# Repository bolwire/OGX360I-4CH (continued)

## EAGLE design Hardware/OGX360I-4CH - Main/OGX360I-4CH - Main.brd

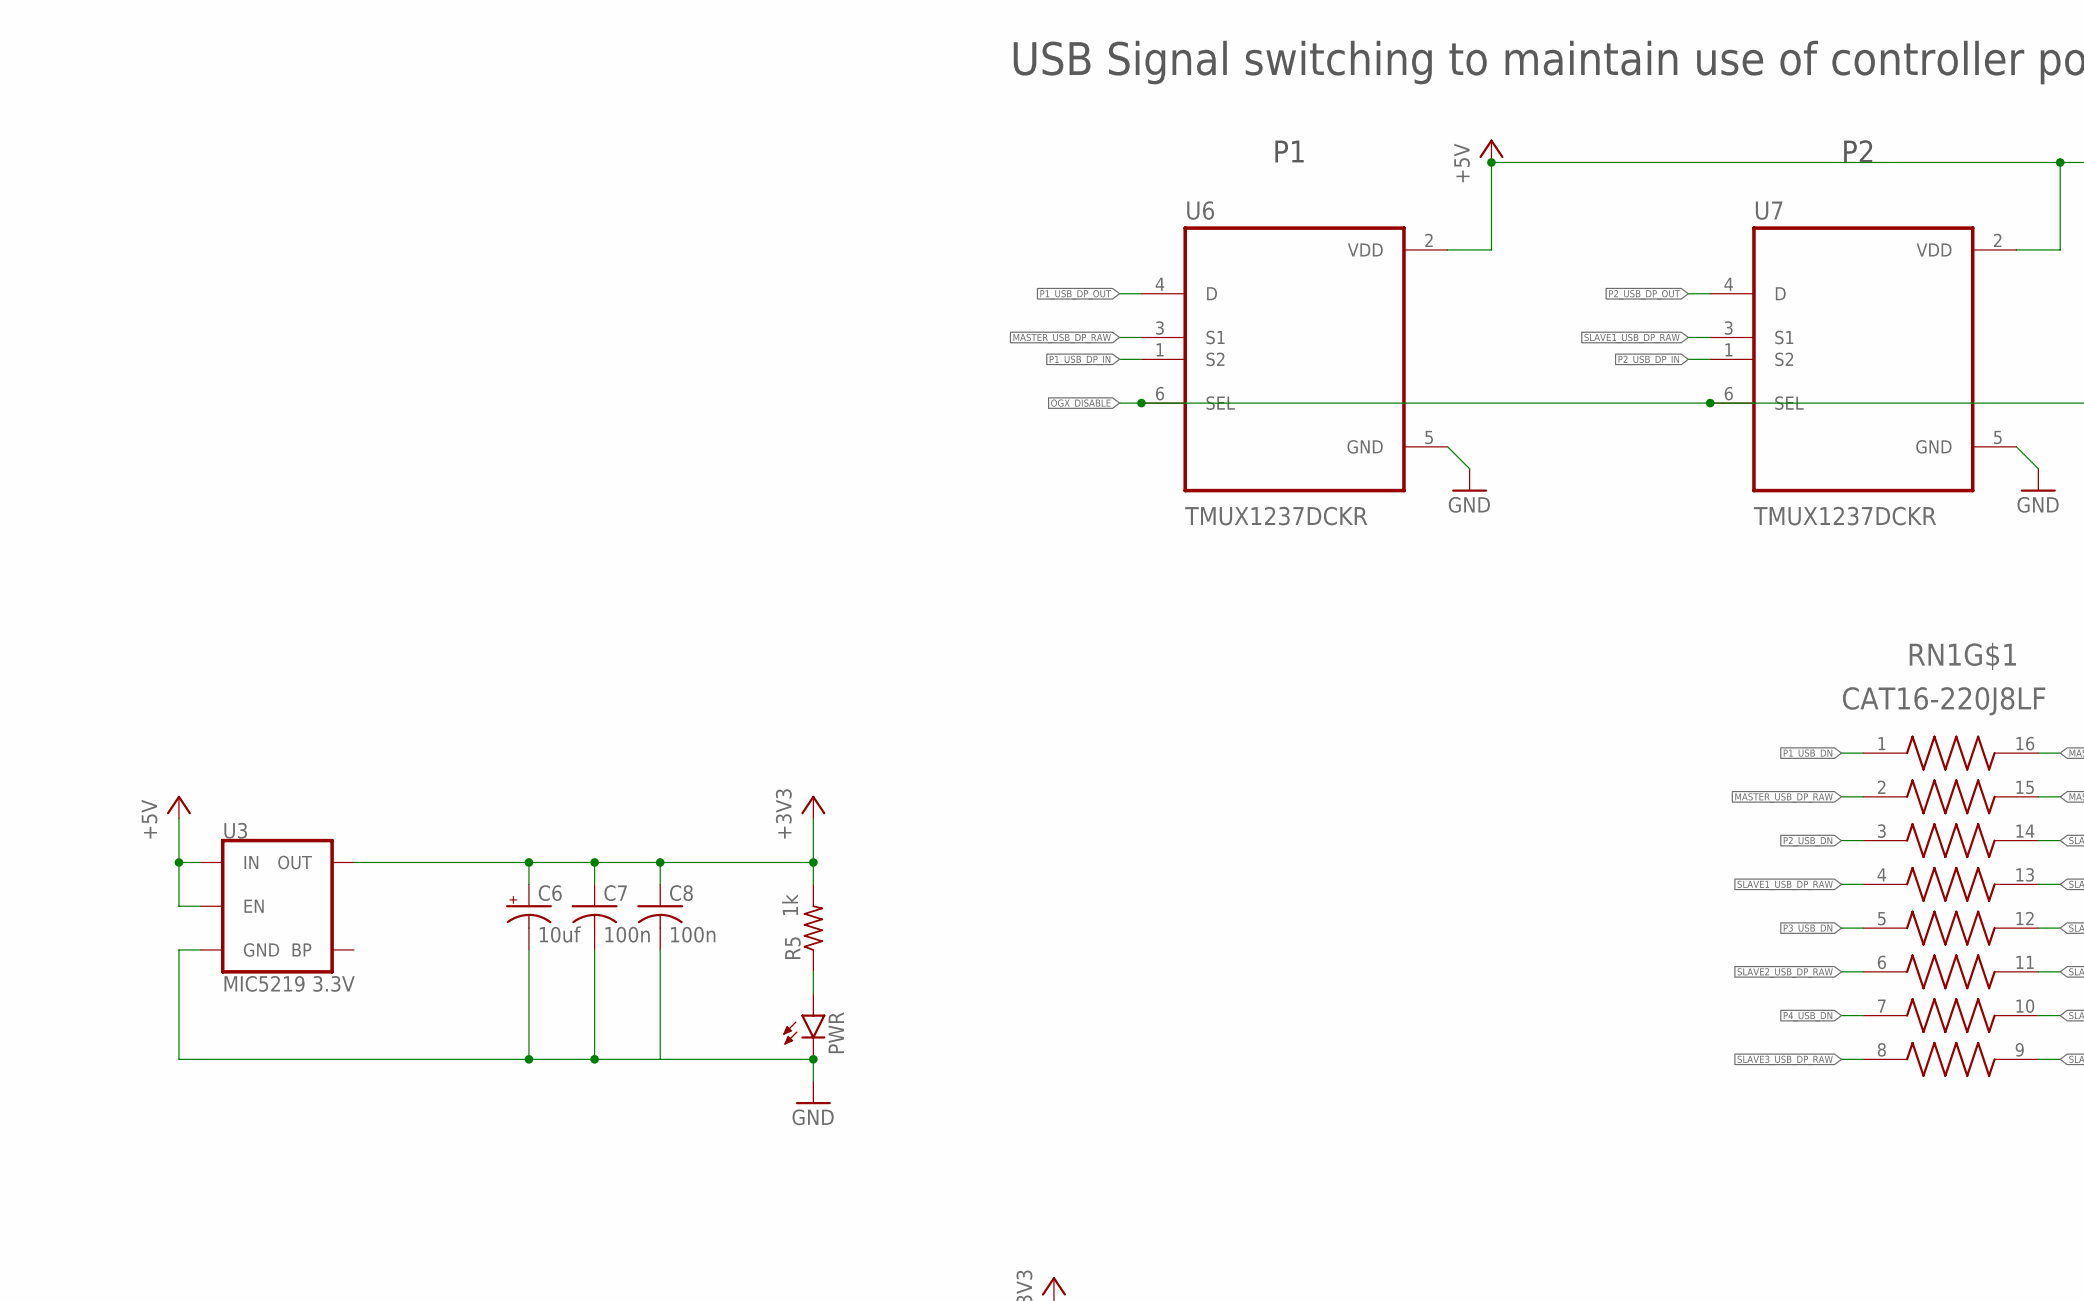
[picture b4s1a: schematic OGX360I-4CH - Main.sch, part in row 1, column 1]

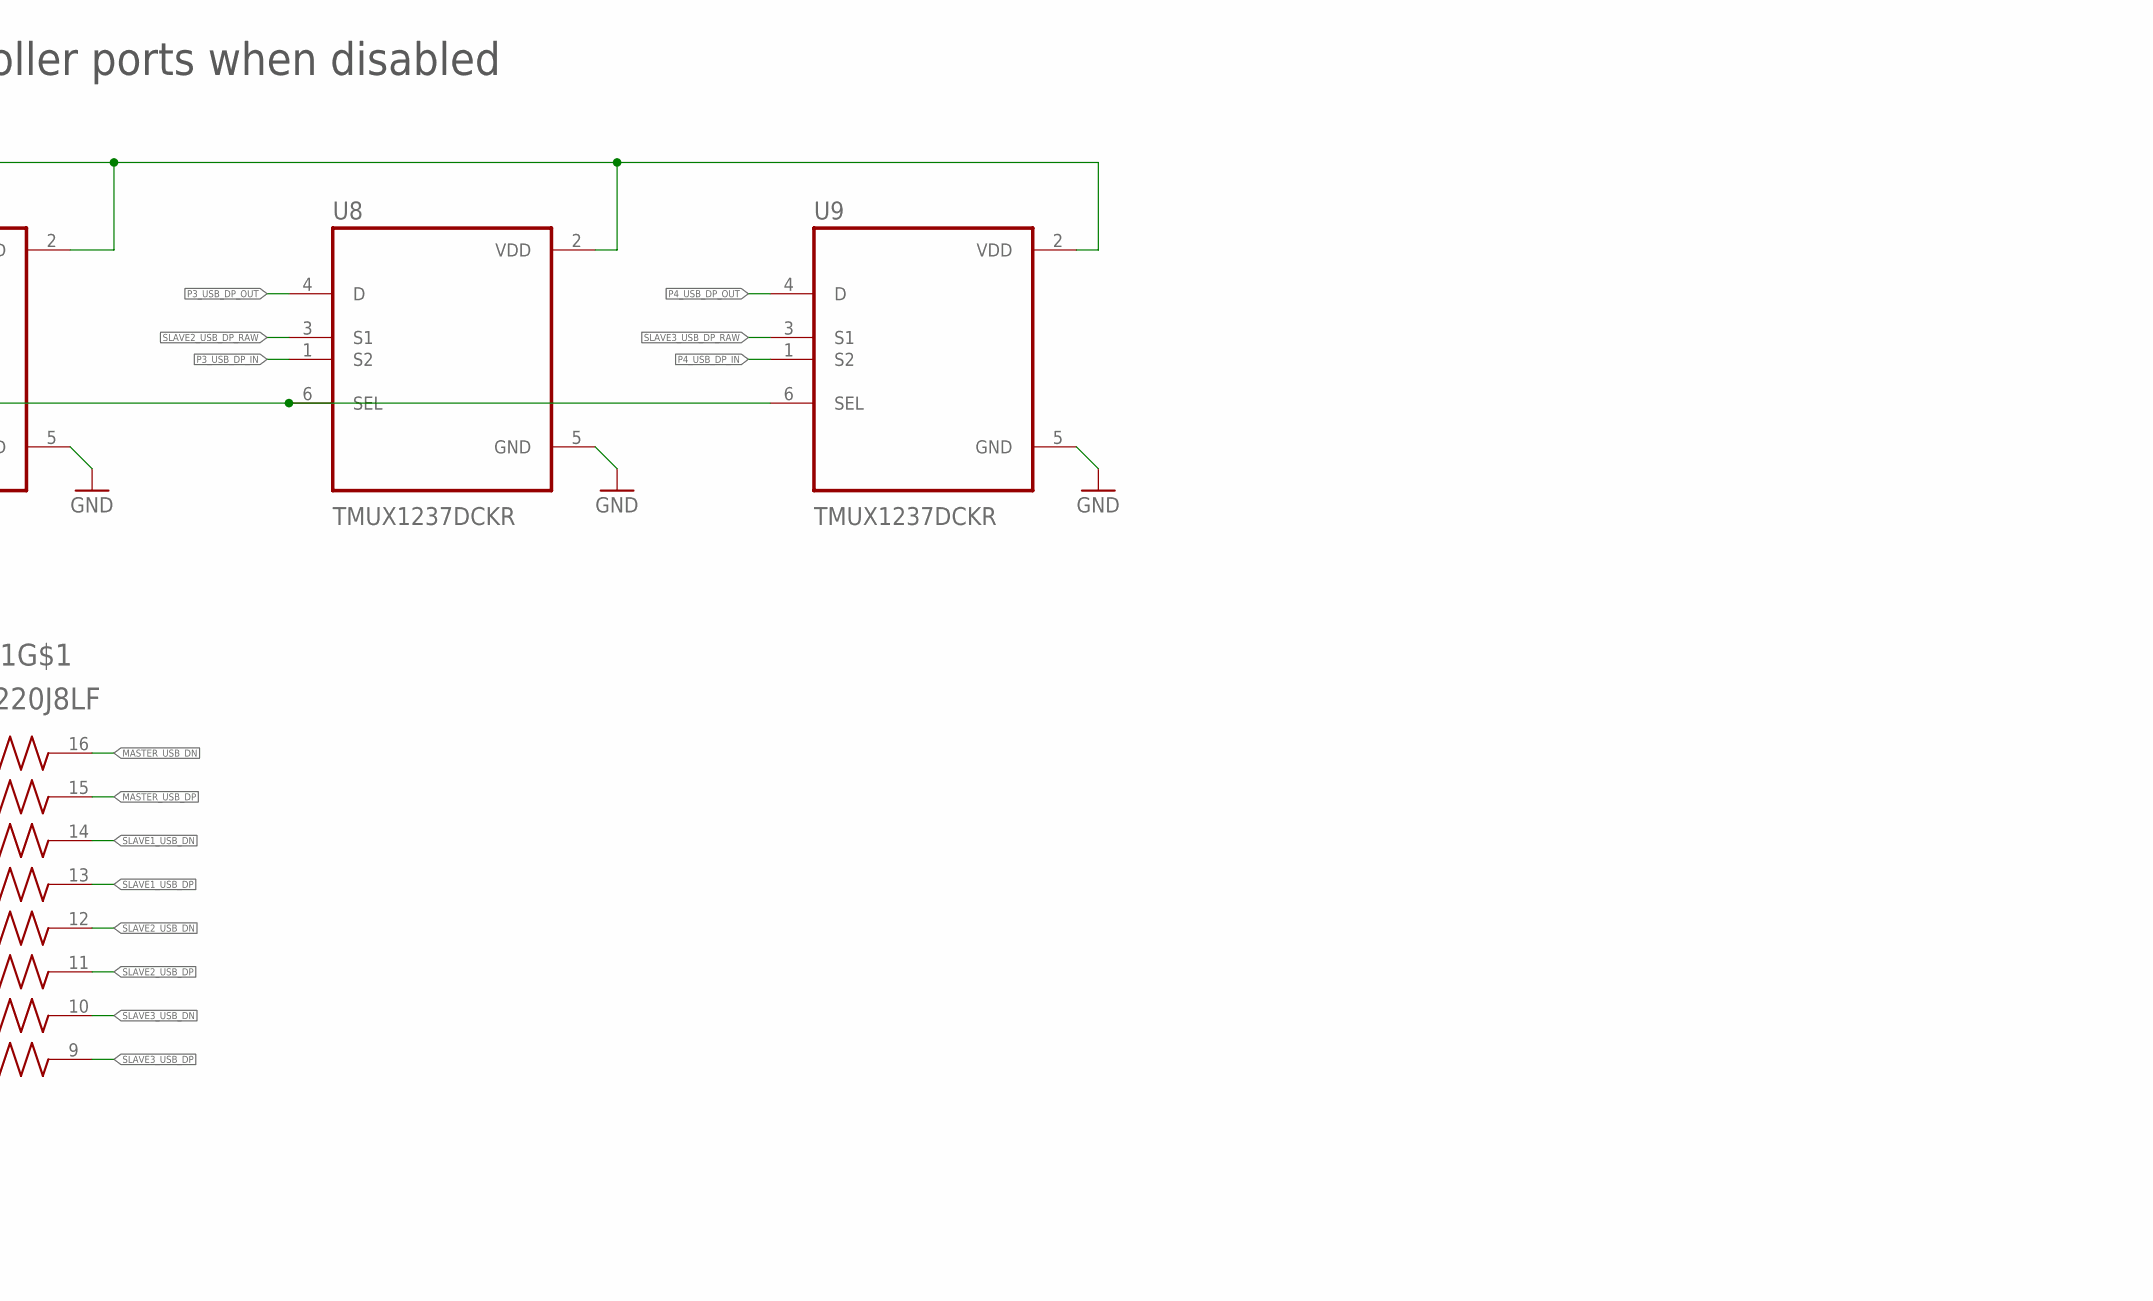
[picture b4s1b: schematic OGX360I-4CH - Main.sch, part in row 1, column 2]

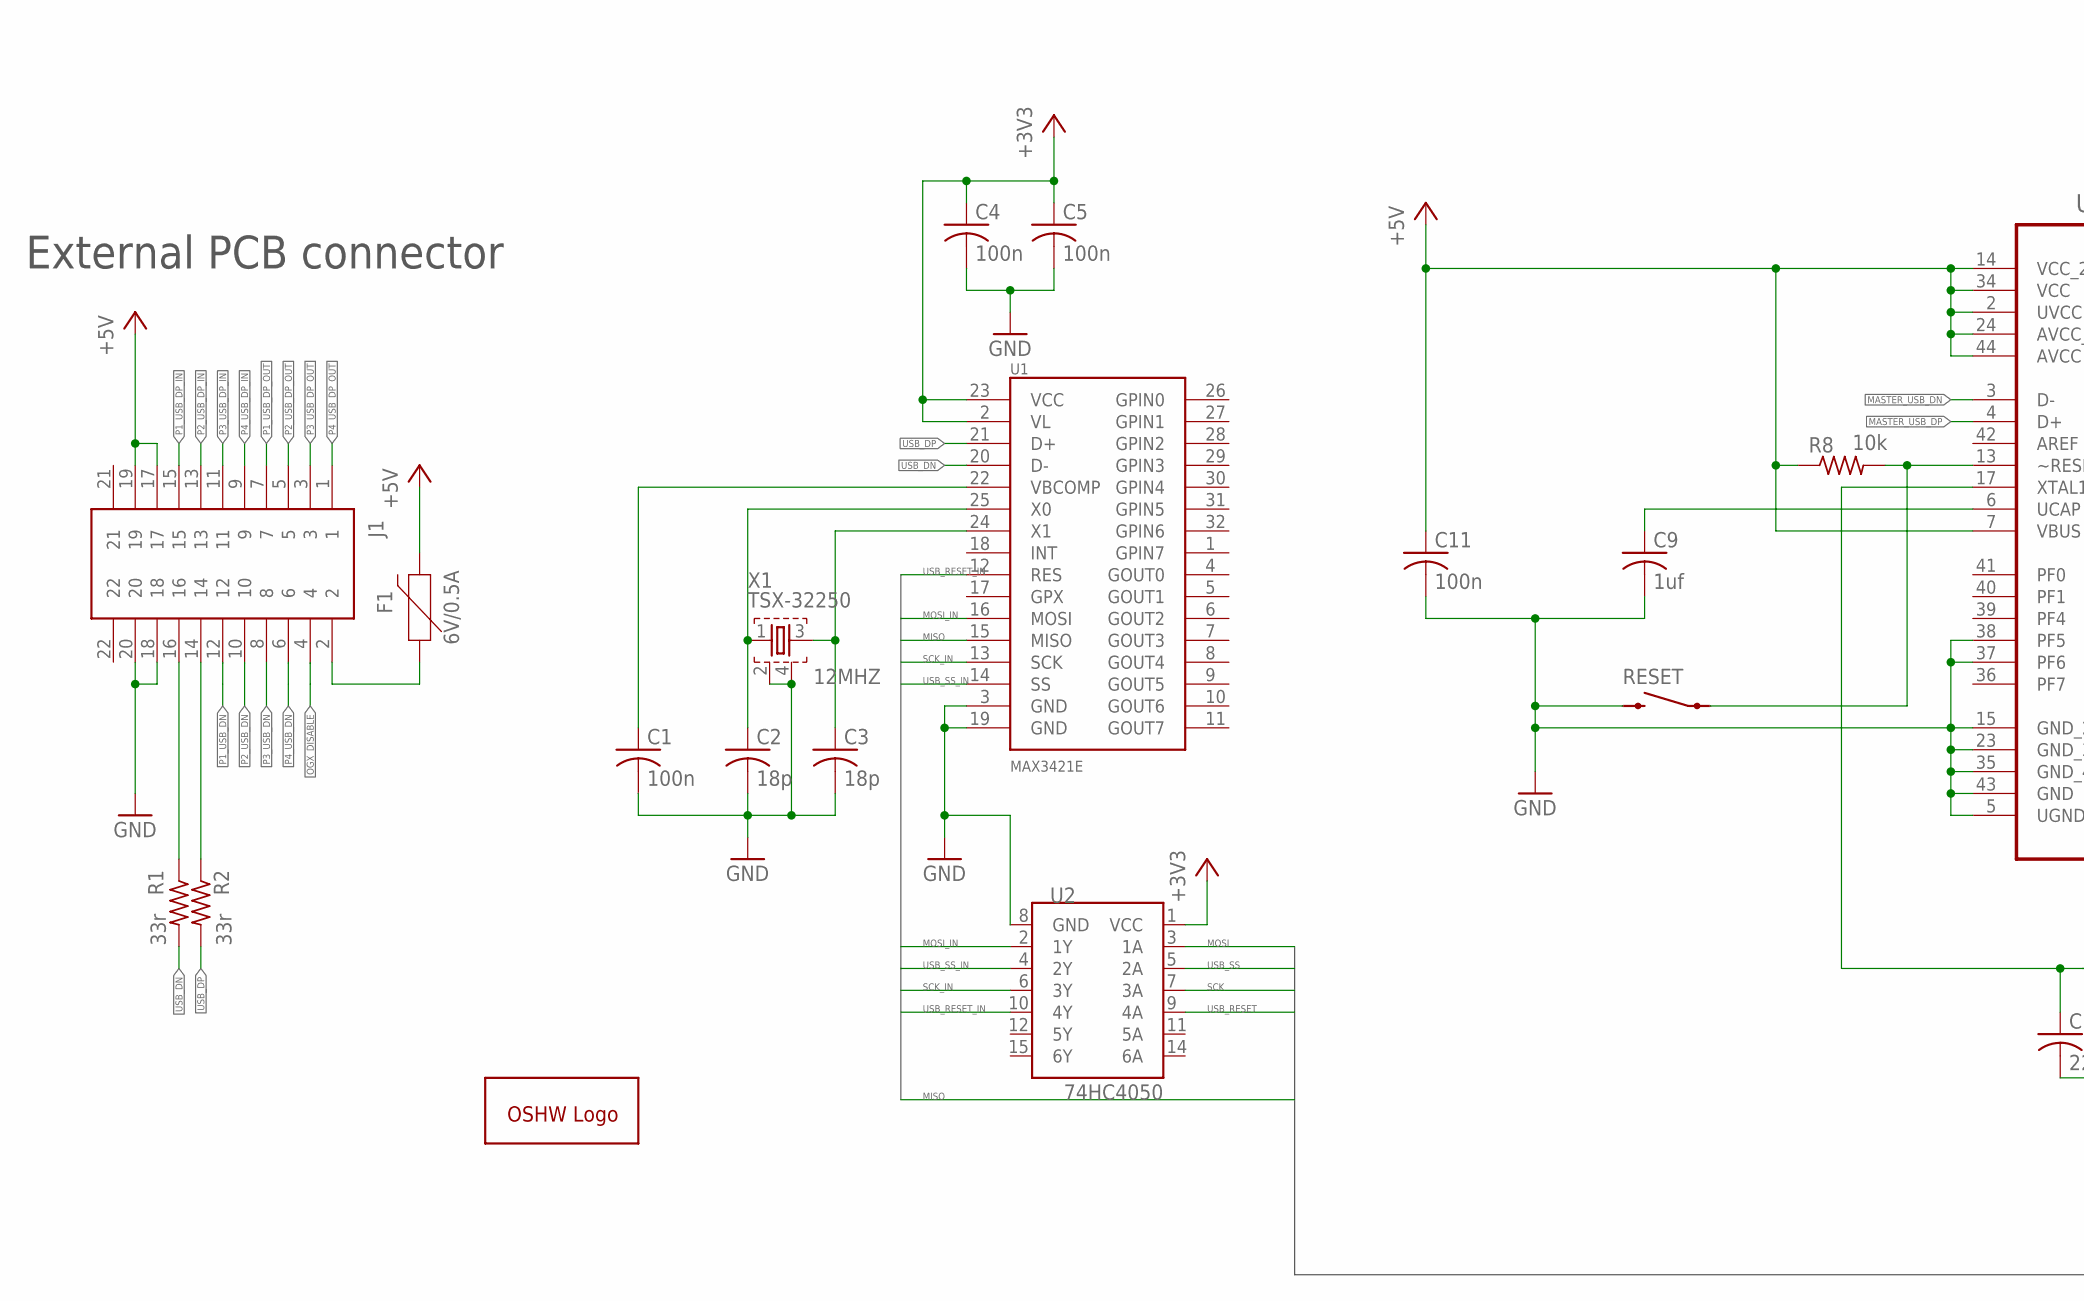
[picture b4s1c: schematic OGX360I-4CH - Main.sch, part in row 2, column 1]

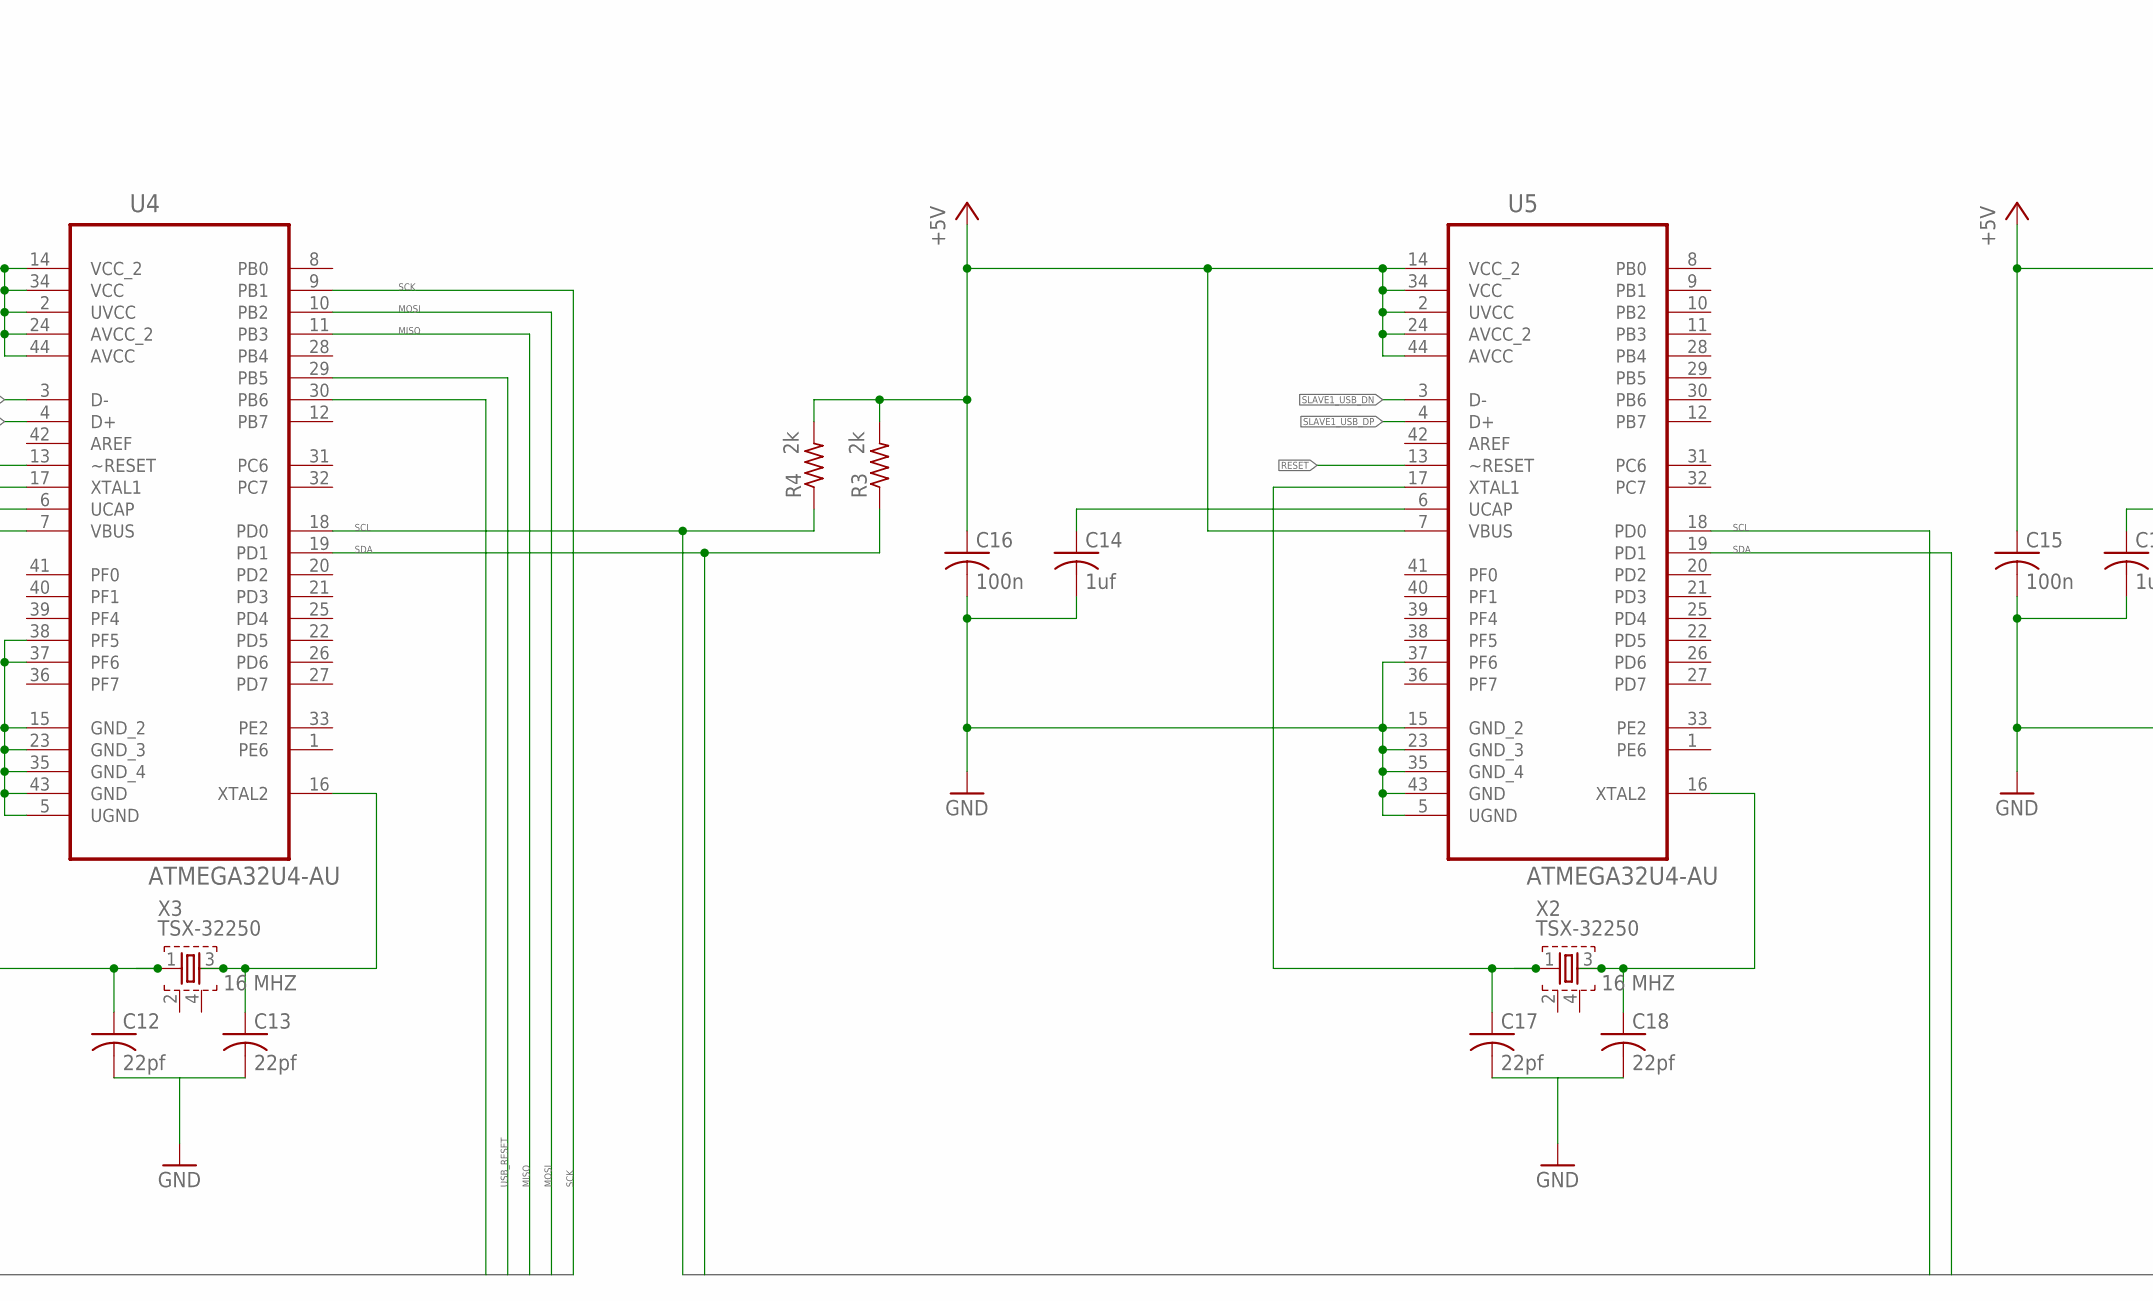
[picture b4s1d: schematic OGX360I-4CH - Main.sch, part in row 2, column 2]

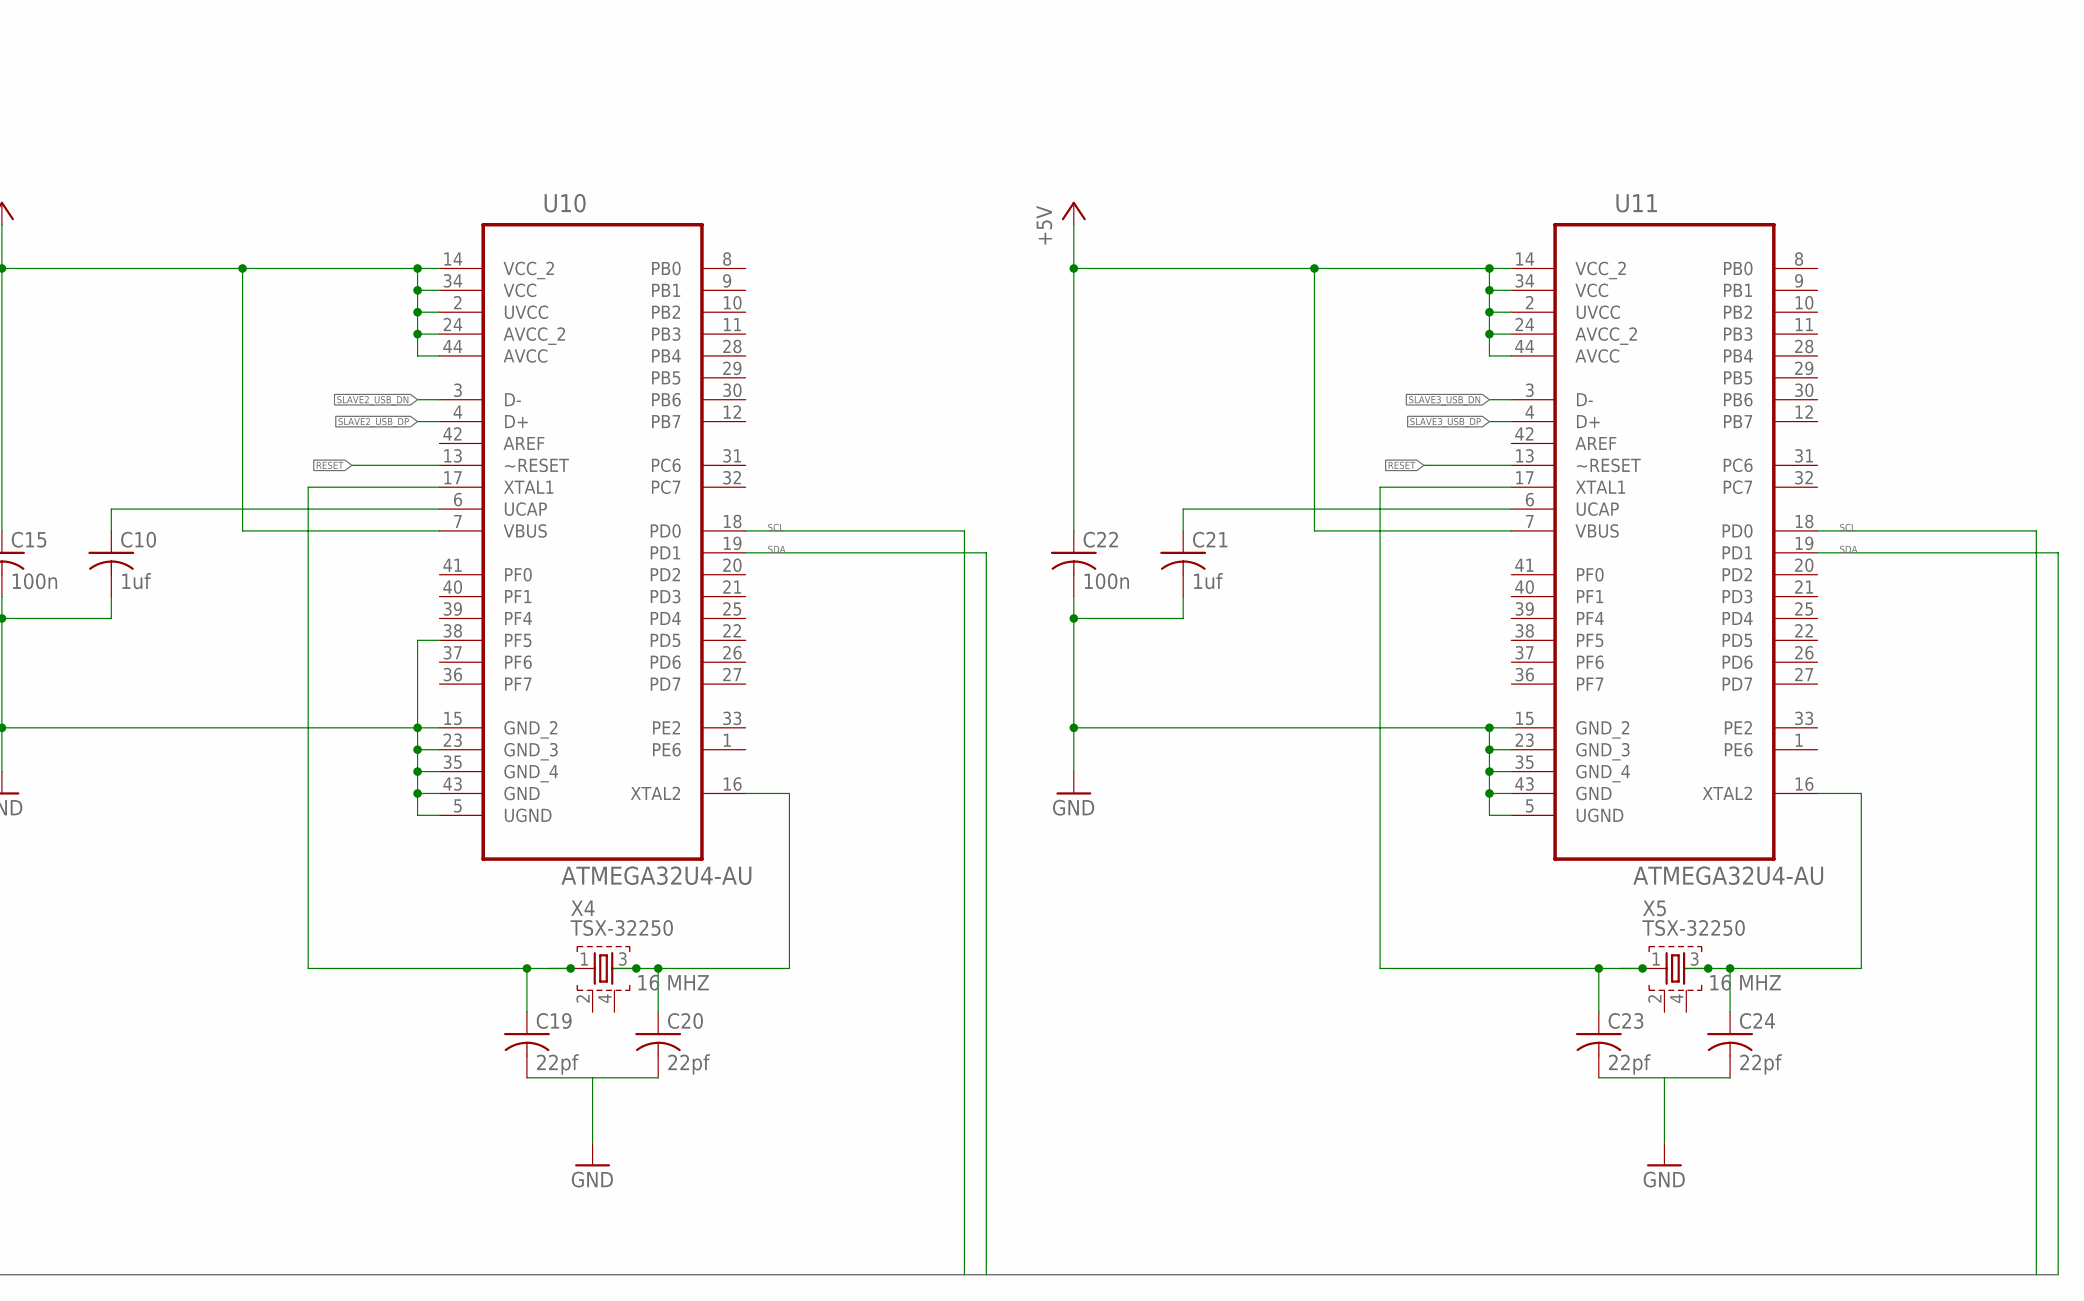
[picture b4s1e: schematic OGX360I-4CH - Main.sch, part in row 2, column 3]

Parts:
C1, C4, C5, C7, C8, C11, C15, C16, C22: 100n; C0805
C2, C3: 18p; C0805
C6: 10uf; 153CLV-0405
C9, C10, C14, C21: 1uf; C0805
C12, C13, C17, C18, C19, C20, C23, C24: 22pf; C0805
F1: 6V/0.5A; 1206
GOLD_ORB_SM1: OSHWLOGOLOGO8MM; OSHW_8MM
J1: SM20B-SRDS-G-TF(LF)(SN); SM20BSRDSGTFLFSN
PWR: LEDCHIP-LED0805; CHIP-LED0805
R1, R2: 33r; M0805
R3, R4: 2k; M0805
R5: 1k; M0805
R8: 10k; M0805
RESET: TL3305AF160QG
RN1: CAT16-220J8LF; RESCAV80P640X160X75-16N
U1: MAX3421E; TQFP32-5MM
U2: 74HC4050; SO16
U3: MIC5219 3.3V; SOT23-5
U4, U5, U10, U11: ATMEGA32U4-AU; QFP80P1200X1200X120-44N
U6, U7, U8, U9: TMUX1237DCKR; SOT65P210X110-6N
X1, X2, X3, X4, X5: TSX-32250; TSX-3225

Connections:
+3V3: C4.1, C5.1, C6.+, C7.1, C8.1, R5.2, U1.2 (VL), U1.23 (VCC), U2.1 (VCC), U3.5 (OUT)
+5V: C11.1, C15.1, C16.1, C22.1, F1.2, J1.17, J1.19, R3.2, R4.2, R8.1, U3.1 (IN), U3.3 (EN), U4.2 (UVCC), U4.7 (VBUS), U4.14 (VCC_2), U4.24 (AVCC_2), U4.34 (VCC), U4.44 (AVCC), U5.2 (UVCC), U5.7 (VBUS), U5.14 (VCC_2), U5.24 (AVCC_2), U5.34 (VCC), U5.44 (AVCC), U6.2 (VDD), U7.2 (VDD), U8.2 (VDD), U9.2 (VDD), U10.2 (UVCC), U10.7 (VBUS), U10.14 (VCC_2), U10.24 (AVCC_2), U10.34 (VCC), U10.44 (AVCC), U11.2 (UVCC), U11.7 (VBUS), U11.14 (VCC_2), U11.24 (AVCC_2), U11.34 (VCC), U11.44 (AVCC)
EXT_USB_DN: J1.16, R1.1
EXT_USB_DP: J1.14, R2.1
FUSED_+5V: F1.1, J1.2
GND: C1.2, C2.2, C3.2, C4.2, C5.2, C6.-, C7.2, C8.2, C9.2, C10.2, C11.2, C12.2, C13.2, C14.2, C15.2, C16.2, C17.2, C18.2, C19.2, C20.2, C21.2, C22.2, C23.2, C24.2, J1.18, J1.20, PWR.C, RESET.P$1, RESET.P$2, U1.3 (GND), U1.19 (GND), U2.8 (GND), U3.2 (GND), U4.5 (UGND), U4.15 (GND_2), U4.23 (GND_3), U4.35 (GND_4), U4.37 (PF6), U4.38 (PF5), U4.43 (GND), U5.5 (UGND), U5.15 (GND_2), U5.23 (GND_3), U5.35 (GND_4), U5.37 (PF6), U5.43 (GND), U6.5 (GND), U7.5 (GND), U8.5 (GND), U9.5 (GND), U10.5 (UGND), U10.15 (GND_2), U10.23 (GND_3), U10.35 (GND_4), U10.38 (PF5), U10.43 (GND), U11.5 (UGND), U11.15 (GND_2), U11.23 (GND_3), U11.35 (GND_4), U11.43 (GND), X1.2, X1.4
MASTER_USB_DN: RN1.16 (R1-2), U4.3 (D-)
MASTER_USB_DP: RN1.15 (R2-2), U4.4 (D+)
MASTER_USB_DP_RAW: RN1.2 (R2-1), U6.3 (S1)
MISO: U1.15 (MISO), U4.11 (PB3)
MOSI: U2.3 (1A), U4.10 (PB2)
MOSI_IN: U1.16 (MOSI), U2.2 (1Y)
unnamed: C13.1, U4.16 (XTAL2), X3.3
unnamed: C3.1, U1.24 (X1), X1.3
unnamed: C10.1, U10.6 (UCAP)
unnamed: PWR.A, R5.1
unnamed: C2.1, U1.25 (X0), X1.1
unnamed: C1.1, U1.22 (VBCOMP)
unnamed: C20.1, U10.16 (XTAL2), X4.3
unnamed: C19.1, U10.17 (XTAL1), X4.1
unnamed: C9.1, U4.6 (UCAP)
unnamed: C21.1, U11.6 (UCAP)
unnamed: C24.1, U11.16 (XTAL2), X5.3
unnamed: C23.1, U11.17 (XTAL1), X5.1
unnamed: C12.1, U4.17 (XTAL1), X3.1
unnamed: C14.1, U5.6 (UCAP)
unnamed: C18.1, U5.16 (XTAL2), X2.3
unnamed: C17.1, U5.17 (XTAL1), X2.1
OGX_DISABLE: J1.4, U6.6 (SEL), U7.6 (SEL), U8.6 (SEL), U9.6 (SEL)
P1_USB_DN: J1.12, RN1.1 (R1-1)
P1_USB_DP_IN: J1.15, U6.1 (S2)
P1_USB_DP_OUT: J1.7, U6.4 (D)
P2_USB_DN: J1.10, RN1.3 (R3-1)
P2_USB_DP_IN: J1.13, U7.1 (S2)
P2_USB_DP_OUT: J1.5, U7.4 (D)
P3_USB_DN: J1.8, RN1.5 (R5-1)
P3_USB_DP_IN: J1.11, U8.1 (S2)
P3_USB_DP_OUT: J1.3, U8.4 (D)
P4_USB_DN: J1.6, RN1.7 (R7-1)
P4_USB_DP_IN: J1.9, U9.1 (S2)
P4_USB_DP_OUT: J1.1, U9.4 (D)
RESET: R8.2, RESET.P$3 (2), RESET.P$4 (2), U4.13 (~RESET), U5.13 (~RESET), U10.13 (~RESET), U11.13 (~RESET)
SCK: U2.7 (3A), U4.9 (PB1)
SCK_IN: U1.13 (SCK), U2.6 (3Y)
SCL: R4.1, U4.18 (PD0), U5.18 (PD0), U10.18 (PD0), U11.18 (PD0)
SDA: R3.1, U4.19 (PD1), U5.19 (PD1), U10.19 (PD1), U11.19 (PD1)
SLAVE1_USB_DN: RN1.14 (R3-2), U5.3 (D-)
SLAVE1_USB_DP: RN1.13 (R4-2), U5.4 (D+)
SLAVE1_USB_DP_RAW: RN1.4 (R4-1), U7.3 (S1)
SLAVE2_USB_DN: RN1.12 (R5-2), U10.3 (D-)
SLAVE2_USB_DP: RN1.11 (R6-2), U10.4 (D+)
SLAVE2_USB_DP_RAW: RN1.6 (R6-1), U8.3 (S1)
SLAVE3_USB_DN: RN1.10 (R7-2), U11.3 (D-)
SLAVE3_USB_DP: RN1.9 (R8-2), U11.4 (D+)
SLAVE3_USB_DP_RAW: RN1.8 (R8-1), U9.3 (S1)
USB_DN: R1.2, U1.20 (D-)
USB_DP: R2.2, U1.21 (D+)
USB_RESET: U2.9 (4A), U4.29 (PB5)
USB_RESET_IN: U1.12 (RES), U2.10 (4Y)
USB_SS: U2.5 (2A), U4.30 (PB6)
USB_SS_IN: U1.14 (SS), U2.4 (2Y)

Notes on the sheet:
12MHZ
16 MHZ
USB Signal switching to maintain use of controller ports when disabled
External PCB connector

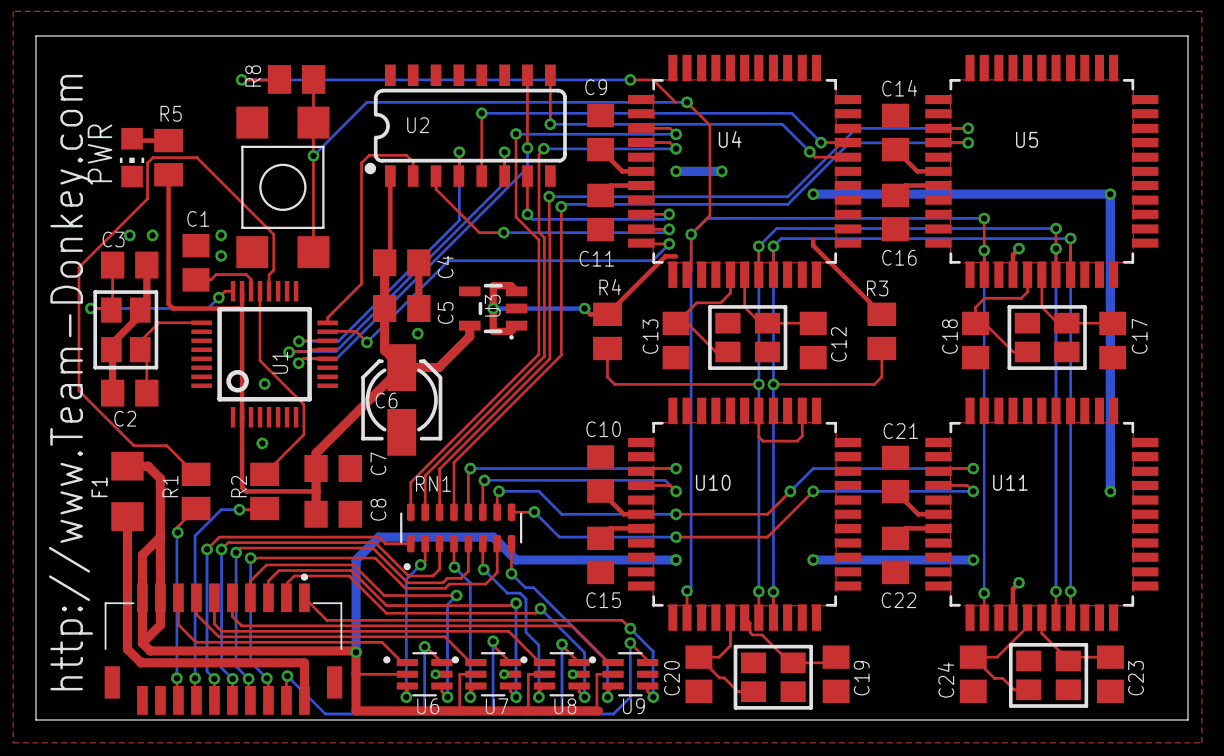
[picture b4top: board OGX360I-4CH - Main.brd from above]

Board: 2 copper layers, 64.0 x 38.0 mm, 52 parts (1 on the bottom side), 61 nets.
